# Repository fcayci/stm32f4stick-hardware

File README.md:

# STM32F4Stick - An STM32F405/STM32F401 based development board - Hardware
This board is intended to be a small bread-board friendly development environment for STM32F4 series microcontrollers. There are different versions some of which are not tested. Please contact me if you see any problems or have any suggestions.

**There are two versions available with slight different mods. Checkout Ver1 or Ver2 branches for latest versions**

### STM32F4Stick VERSIONS:

#### VERSION 2:

* 1.84 x 1.02 inches board size
* STM32F405RG ARM Microcontroller
* STM32F401 ARM Microcontroller compatibility
* 16 MHz HSE Oscillator
* MiniUSB connector for power/programming (through bootloader)
* SD Card slot connected in SPI mode
* nRF24L01+ 2.4GHz radio module compatible header
* 1 x 16-pin breakout header and 1 x 6-pin header on both sides for easy breadboard development
* 2 x LEDs + 1 Push button
* Reset button
* Optional pull-ups on pins A10, B5, B11, and C11 for reliable USB bootloader
* Jump pads on BOOT0 pin, and push button on BOOT1 pin (Also act as a GPIO pin)

#### VERSION 1:
* 1.84 x 1.02 inches board size
* STM32F405RG ARM Microcontroller
* STM32F401 ARM Microcontroller compatibility
* 16 MHz HSE Oscillator
* MiniUSB connector for power/programming (through bootloader)
* SD Card slot connected in SPI mode
* 2 x 16-pin breakout headers on both sides for easy breadboard development
* 2 x LEDs + 1 Push button
* Reset button
* Optional pull-up / pull-downs on pins A10, B5, B11, and C11 for reliable USB bootloader
* Jump pads on BOOT0 pin, and push button on BOOT1 pin (Also act as a GPIO pin)

### Possible Future Changes:
* FIX:
  * Locate and connect DAC pin(s) to the extension headers if they are not broken out already
* NEW:
  * Connect SD Card in SDIO mode
  * Add an I2C compatible chip for an on-board I2C part. Possibly an MPU6050/9150 part if it fits
  * Change to a Micro USB connector

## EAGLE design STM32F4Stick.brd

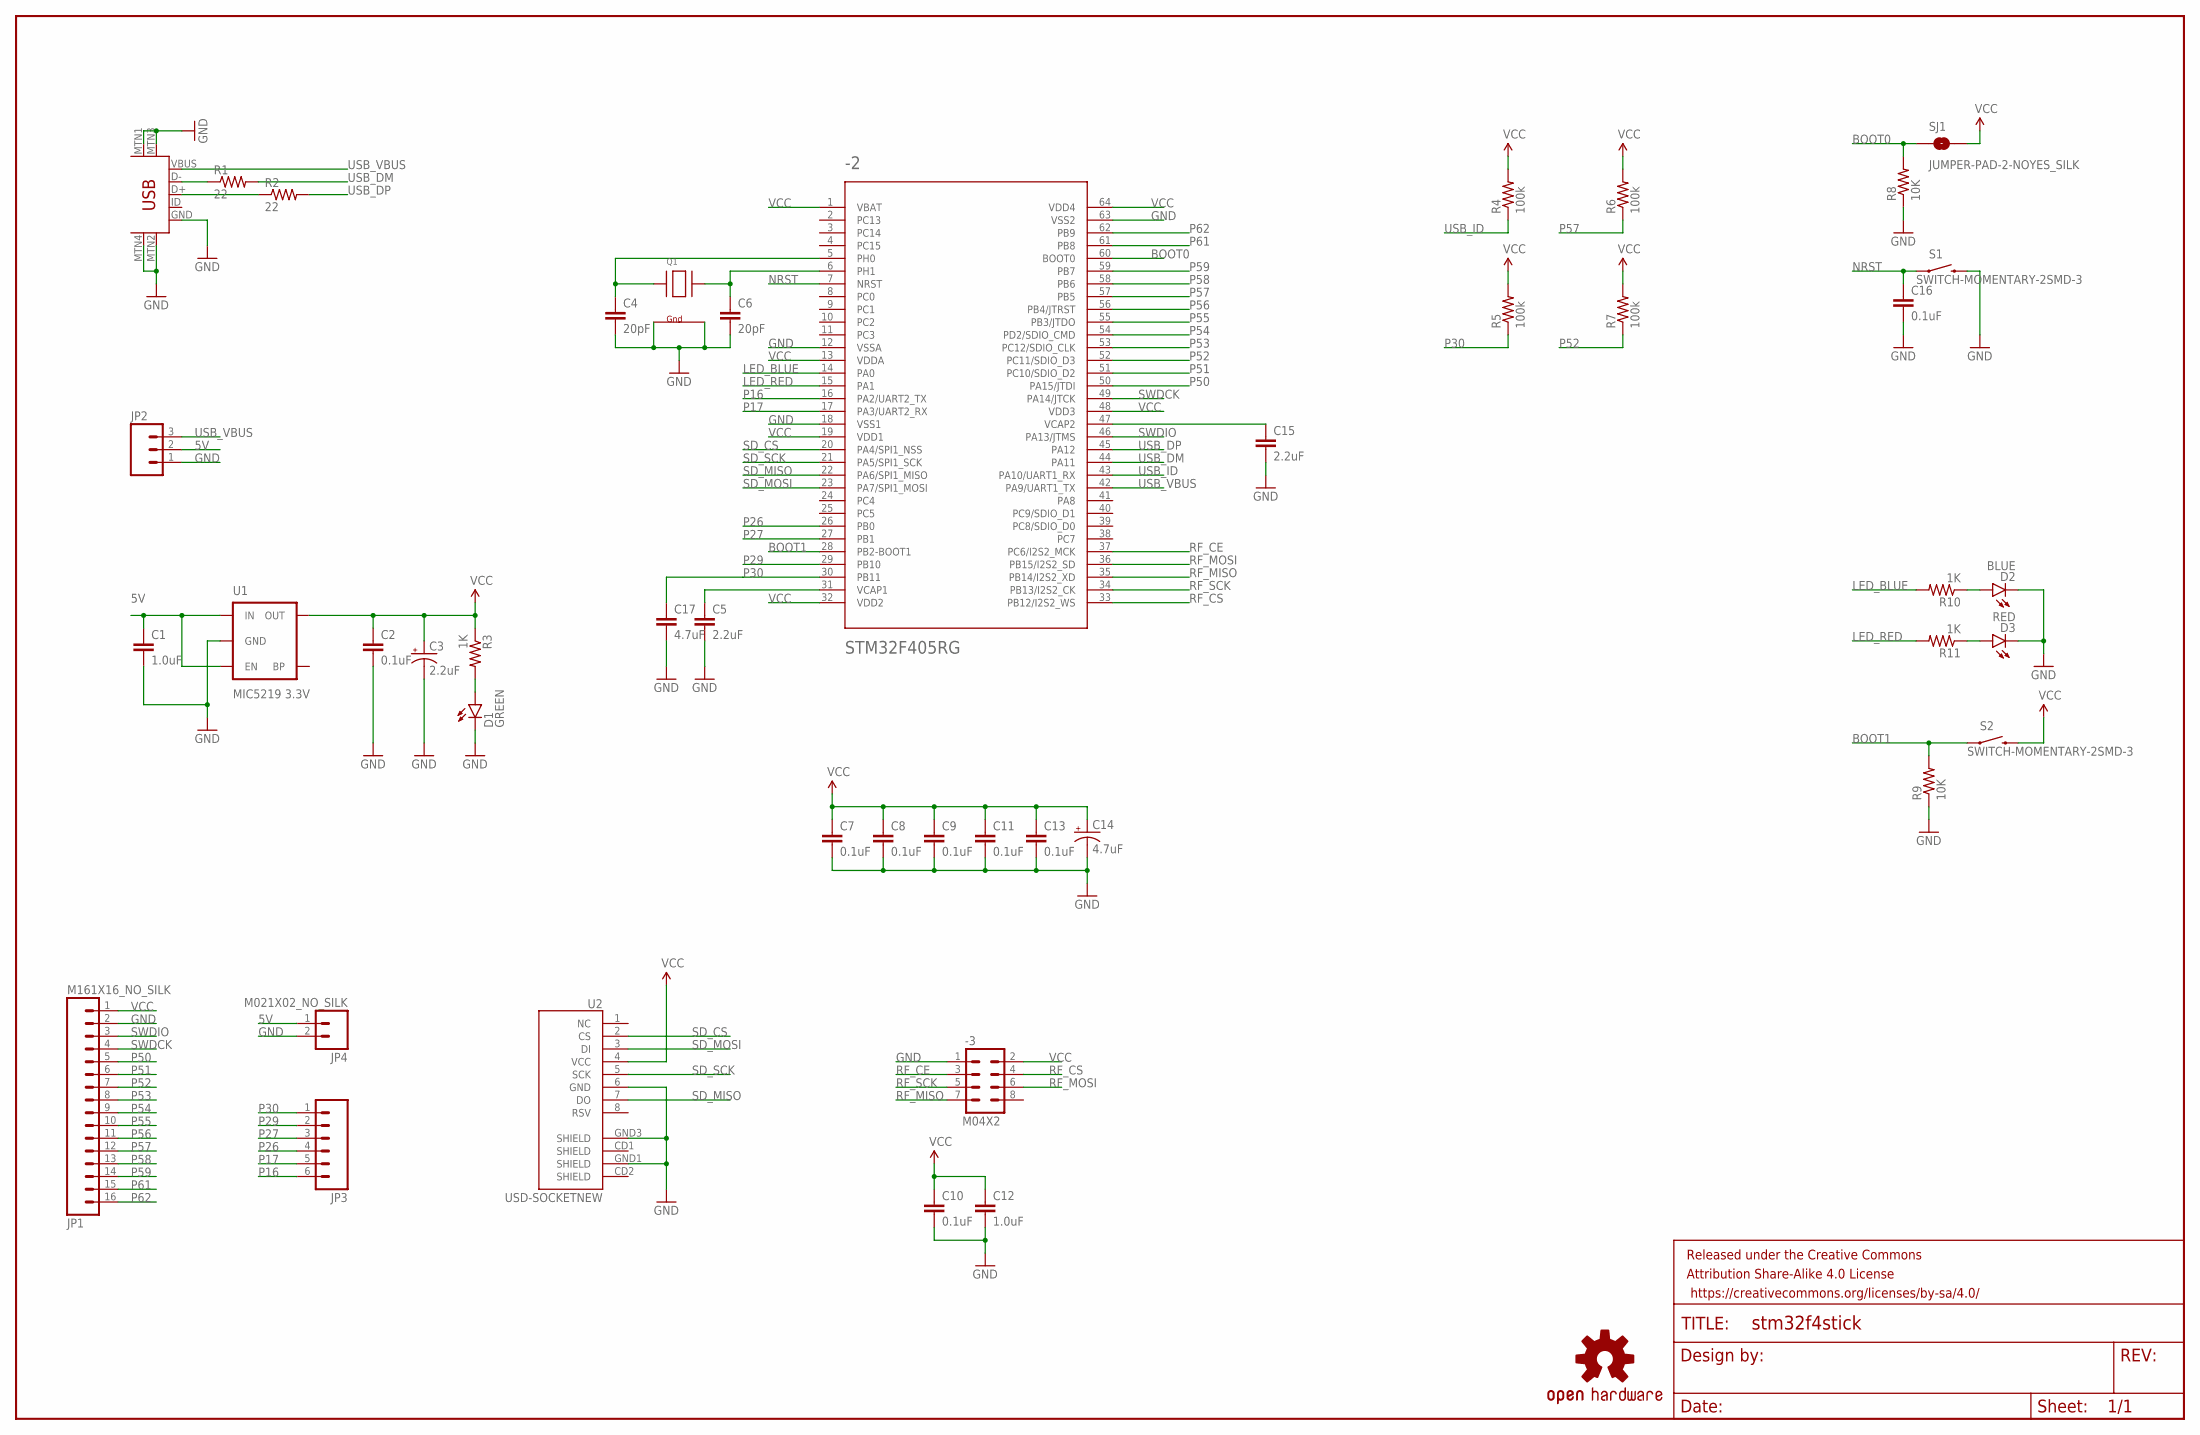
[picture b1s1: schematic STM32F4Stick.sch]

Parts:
-1: USB-MINIB-5PIN; USB-MINIB
-2: STM32F405RG; TQFP64
-3: M04X2; 2X4
C1, C12: 1.0uF; 0603-CAP
C2, C7, C8, C9, C10, C11, C13, C16: 0.1uF; 0603-CAP
C3: 2.2uF; EIA3216
C4, C6: 20pF; 0603-CAP
C5, C15: 2.2uF; 0603-CAP
C14: 4.7uF; EIA3216
C17: 4.7uF; 0603-CAP
D1: GREEN; LED-0603
D2: BLUE; LED-0603
D3: RED; LED-0603
FRAME1: FRAME-LEDGER; CREATIVE_COMMONS
JP1: M161X16_NO_SILK; 1X16_NO_SILK
JP2: M031X03_NO_SILK; 1X03_NO_SILK
JP3: M06NO_SILK; 1X06_NO_SILK
JP4: M021X02_NO_SILK; 1X02_NO_SILK
LOGO1: OSHW-LOGOM; OSHW-LOGO-M
Q1: XTAL-4-3225; NX3225
R1, R2: 22; 0603-RES
R3, R10, R11: 1K; 0603-RES
R4, R5, R6, R7: 100k; 0603-RES
R8, R9: 10K; 0603-RES
S1, S2: SWITCH-MOMENTARY-2SMD-3; TACTILE_SWITCH_SMD-3
SJ1: JUMPER-PAD-2-NOYES_SILK; PAD-JUMPER-2-NO_YES_SILK
U1: MIC5219 3.3V; SOT23-5
U2: USD-SOCKETNEW; MICRO-SD-SOCKET-PP

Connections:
5V: C1.1, JP2.2, JP4.1, U1.1 (IN), U1.3 (EN)
BOOT0: -2.60 (BOOT0), R8.2, SJ1.1
BOOT1: -2.28 (PB2-BOOT1), R9.2, S2.1
GND: -1.GND, -1.MTN1 (MTN2), -1.MTN2 (MTN3), -1.MTN3 (MTN1), -1.MTN4, -2.12 (VSSA), -2.18 (VSS1), -2.63 (VSS2), -3.1, C1.2, C2.2, C3.C (-), C4.2, C5.2, C6.2, C7.2, C8.2, C9.2, C10.2, C11.2, C12.2, C13.2, C14.C (-), C15.2, C16.2, C17.2, D1.C, D2.C, D3.C, JP1.2, JP2.1, JP4.2, Q1.2 (G2), Q1.4 (G1), R8.1, R9.1, S1.4 (2), U1.2 (GND), U2.6 (GND), U2.GND1 (SHIELD), U2.GND3 (SHIELD)
LED_BLUE: -2.14 (PA0), R10.2
LED_RED: -2.15 (PA1), R11.2
unnamed: -2.31 (VCAP1), C5.1
unnamed: -2.5 (PH0), C4.1, Q1.1 (X1)
unnamed: -2.6 (PH1), C6.1, Q1.3 (X2)
unnamed: -2.47 (VCAP2), C15.1
unnamed: D2.A, R10.1
unnamed: D3.A, R11.1
unnamed: D1.A, R3.2
unnamed: -1.D-, R1.1
unnamed: -1.D+, R2.1
NRST: -2.7 (NRST), C16.1, S1.1
P16: -2.16 (PA2/UART2_TX), JP3.6
P17: -2.17 (PA3/UART2_RX), JP3.5
P26: -2.26 (PB0), JP3.4
P27: -2.27 (PB1), JP3.3
P29: -2.29 (PB10), JP3.2
P30: -2.30 (PB11), C17.1, JP3.1, R5.1
P50: -2.50 (PA15/JTDI), JP1.5
P51: -2.51 (PC10/SDIO_D2), JP1.6
P52: -2.52 (PC11/SDIO_D3), JP1.7, R7.1
P53: -2.53 (PC12/SDIO_CLK), JP1.8
P54: -2.54 (PD2/SDIO_CMD), JP1.9
P55: -2.55 (PB3/JTDO), JP1.10
P56: -2.56 (PB4/JTRST), JP1.11
P57: -2.57 (PB5), JP1.12, R6.1
P58: -2.58 (PB6), JP1.13
P59: -2.59 (PB7), JP1.14
P61: -2.61 (PB8), JP1.15
P62: -2.62 (PB9), JP1.16
RF_CE: -2.37 (PC6/I2S2_MCK), -3.3
RF_CS: -2.33 (PB12/I2S2_WS), -3.4
RF_MISO: -2.35 (PB14/I2S2_XD), -3.7
RF_MOSI: -2.36 (PB15/I2S2_SD), -3.6
RF_SCK: -2.34 (PB13/I2S2_CK), -3.5
SD_CS: -2.20 (PA4/SPI1_NSS), U2.2 (CS)
SD_MISO: -2.22 (PA6/SPI1_MISO), U2.7 (DO)
SD_MOSI: -2.23 (PA7/SPI1_MOSI), U2.3 (DI)
SD_SCK: -2.21 (PA5/SPI1_SCK), U2.5 (SCK)
SWDCK: -2.49 (PA14/JTCK), JP1.4
SWDIO: -2.46 (PA13/JTMS), JP1.3
USB_DM: -2.44 (PA11), R1.2
USB_DP: -2.45 (PA12), R2.2
USB_ID: -2.43 (PA10/UART1_RX), R4.1
USB_VBUS: -1.VBUS, -2.42 (PA9/UART1_TX), JP2.3
VCC: -2.1 (VBAT), -2.13 (VDDA), -2.19 (VDD1), -2.32 (VDD2), -2.48 (VDD3), -2.64 (VDD4), -3.2, C2.1, C3.A (+), C7.1, C8.1, C9.1, C10.1, C11.1, C12.1, C13.1, C14.A (+), JP1.1, R3.1, R4.2, R5.2, R6.2, R7.2, S2.4 (2), SJ1.2, U1.5 (OUT), U2.4 (VCC)

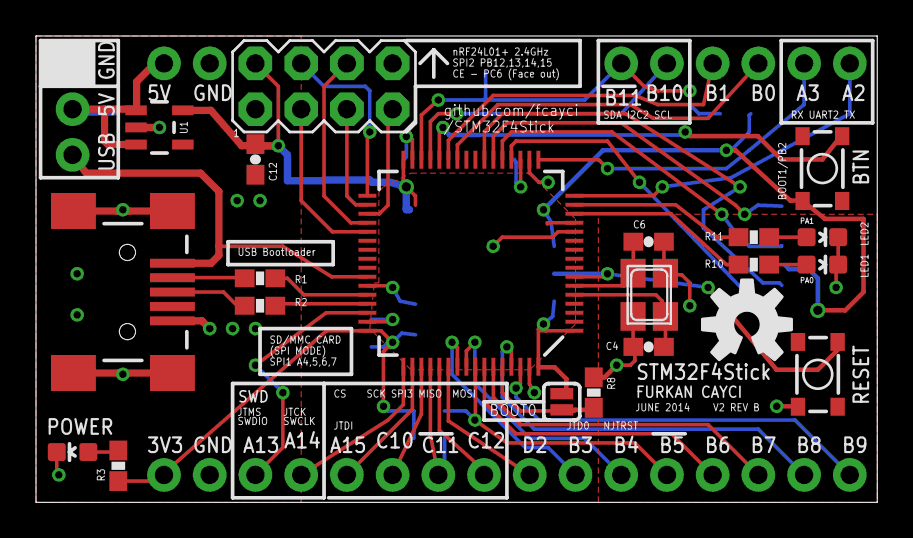
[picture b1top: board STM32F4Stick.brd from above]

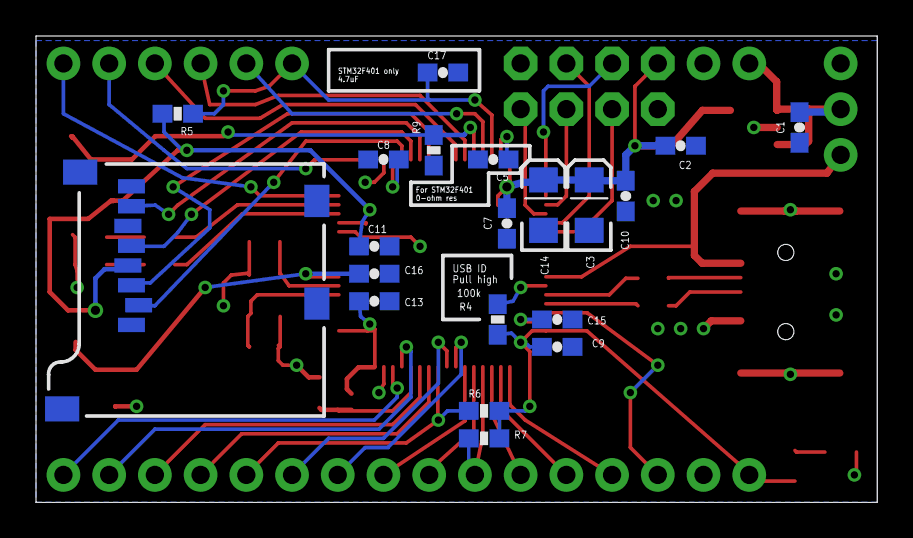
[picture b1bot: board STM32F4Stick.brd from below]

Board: 2 copper layers, 46.7 x 25.9 mm, 46 parts (20 on the bottom side), 50 nets.

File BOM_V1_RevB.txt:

Partlist exported from /Users/furkan/workcenter/eagle/projects/STM32F4Stick/STM32F4Stick.sch at 7/10/14 1:54 AM

Part   Value                   Device                  Package                  Description
-1     USB-MINIB-5PIN          USB-MINIB-5PIN          USB-MINIB                Mini-USB "B" connect
-2     STM32F405RG             STM32F405RG             TQFP64                   ARM DSP Chip used on
C1     1.0uF                   1.0UF-16V-10%(0603)     0603-CAP                 CAP-00868
C2     0.1uF                   0.1UF-25V-5%(0603)      0603-CAP                 CAP-08604
C3     2.2uF                   CAP_POL1206             EIA3216                  Capacitor Polarized
C4     12pF                    12PF-50V-5%(0603)       0603-CAP                 CAP-09137
C5     2.2uF                   2.2UF-10V-20%(0603)     0603-CAP                 CAP-07888
C6     12pF                    12PF-50V-5%(0603)       0603-CAP                 CAP-09137
C7     0.1uF                   0.1UF-25V-5%(0603)      0603-CAP                 CAP-08604
C8     0.1uF                   0.1UF-25V-5%(0603)      0603-CAP                 CAP-08604
C9     0.1uF                   0.1UF-25V-5%(0603)      0603-CAP                 CAP-08604
C10    0.1uF                   0.1UF-25V-5%(0603)      0603-CAP                 CAP-08604
C11    0.1uF                   0.1UF-25V-5%(0603)      0603-CAP                 CAP-08604
C12    4.7uF                   CAP_POL1206             EIA3216                  Capacitor Polarized
C13    2.2uF                   2.2UF-10V-20%(0603)     0603-CAP                 CAP-07888
C14    0.1uF                   0.1UF-25V-5%(0603)      0603-CAP                 CAP-08604
C15    0.1uF                   0.1UF-25V-5%(0603)      0603-CAP                 CAP-08604
D1     GREEN                   LED-GREEN0603           LED-0603                 Various green LEDs
D2     BLUE                    LED-BLUE0603            LED-0603                 Blue LEDs for produc
D3     RED                     LED-RED0603             LED-0603                 Assorted Red LEDs
FRAME1 FRAME-LEDGER            FRAME-LEDGER            CREATIVE_COMMONS         Schematic Frame
JP1    M161X16_NO_SILK         M161X16_NO_SILK         1X16_NO_SILK             1x16 .1" header
JP2                            M031X03_NO_SILK         1X03_NO_SILK             Header 3
JP3    M161X16_NO_SILK         M161X16_NO_SILK         1X16_NO_SILK             1x16 .1" header
LOGO1  OSHW-LOGOM              OSHW-LOGOM              OSHW-LOGO-M              Open Source Hardware
Q1                             XTAL-4-3225             NX3225                   Classic 4-pin 3.2 x
R1     22                      22OHM1/10W1%(0603)      0603-RES                 RES-08698
R2     22                      22OHM1/10W1%(0603)      0603-RES                 RES-08698
R3     1K                      1KOHM1/10W1%(0603)      0603-RES                 RES-07856
R4     100k                    100KOHM1/10W1%(0603)    0603-RES                 RES-07828
R5     100k                    100KOHM1/10W1%(0603)    0603-RES                 RES-07828
R6     100k                    100KOHM1/10W1%(0603)    0603-RES                 RES-07828
R7     100k                    100KOHM1/10W1%(0603)    0603-RES                 RES-07828
R8     10K                     10KOHM1/10W1%(0603)0603 0603-RES                 RES-00824
R9     10K                     10KOHM1/10W1%(0603)0603 0603-RES                 RES-00824
R10    1K                      1KOHM1/10W1%(0603)      0603-RES                 RES-07856
R11    1K                      1KOHM1/10W1%(0603)      0603-RES                 RES-07856
S1     SWITCH-MOMENTARY-2SMD-3 SWITCH-MOMENTARY-2SMD-3 TACTILE_SWITCH_SMD-3     Various NO switches-
S2     SWITCH-MOMENTARY-2SMD-3 SWITCH-MOMENTARY-2SMD-3 TACTILE_SWITCH_SMD-3     Various NO switches-
SJ1    JUMPER-PAD-2-NOYES_SILK JUMPER-PAD-2-NOYES_SILK PAD-JUMPER-2-NO_YES_SILK
U1     MIC5219 3.3V            V_REG_MIC52193.3V       SOT23-5                  V_REG MIC5219
U2     USD-SOCKETNEW           USD-SOCKETNEW           MICRO-SD-SOCKET-PP       microSD Socket

Additional for STM32F401
C5     0                       0OHM1/10W1%(0603)       0603-RES                 RES-07828
C13    0                       0OHM1/10W1%(0603)       0603-RES                 RES-07828
R5     4.7uF                   4.7UF-10V-10%(0603)     0603-CAP                 CAP-07888

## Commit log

2014-06-29 STM32F405 ARM Development Board. Schematic RevA. Should have everything to get the chip working.
2014-06-29 Board layout is almost complete. Needs extension header pins and silkscreen stuff.
2014-06-30 Extension header additions to schematic. Routing is complete on the board. The second extension header connections needs to be added.
2014-06-30 Added SD-Card. Still need to route the extension pins.
2014-06-30 Finished Schematic / Board layout. Silkscreen needs to be added
2014-06-30 Final version for Rev A.
2014-06-30 Small fixes to the usb resistors and a component might get in the way of SD card slot.
2014-06-30 Final Rev B. Added nRF24L01+ 2.4GHz radio compatible header. Got rid of some of the extension headers. Check out RevA if you do not need to use nRF24L01+ radio but instead have extension headers.
2014-07-03 Readme additions. Added a lot of information about V1 and V2 boards.
2014-07-03 Readme fixes for tables
2014-07-09 adeed STM32F401 chip support to schematic only
2014-07-10 V2 RevB final. Finalize stm32f401 support on version 2 board.
2014-07-10 Version 1 Rev B. Added STM32F401 support. Added Readme. Added image. Added libraries. Added BOM.
2014-07-10 Version 2 RevB. Added BOM. Added RevB images. Added fab files. Readme changes.
2014-07-10 master is now only for tracking versions/changelogs. No board files.
2014-07-16 Ver2 RevB. Made changes to some silkscreen lines thinner.
2014-07-19 version 3 still in development. playing with mpu6050/9150 module to see if one can fit
2014-07-21 Readme additions. Picture additions
2014-07-23 button fix

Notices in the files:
parts and their libraries:
SparkFun-DigitalIC: Licensing: Creative Commons ShareAlike 4.0 International - https://creativecommons.org/licenses/by-sa/4.0
SparkFun-Aesthetics: Released under the Creative Commons Attribution Share-Alike 4.0 License
SparkFun-Aesthetics: https://creativecommons.org/licenses/by-sa/4.0
